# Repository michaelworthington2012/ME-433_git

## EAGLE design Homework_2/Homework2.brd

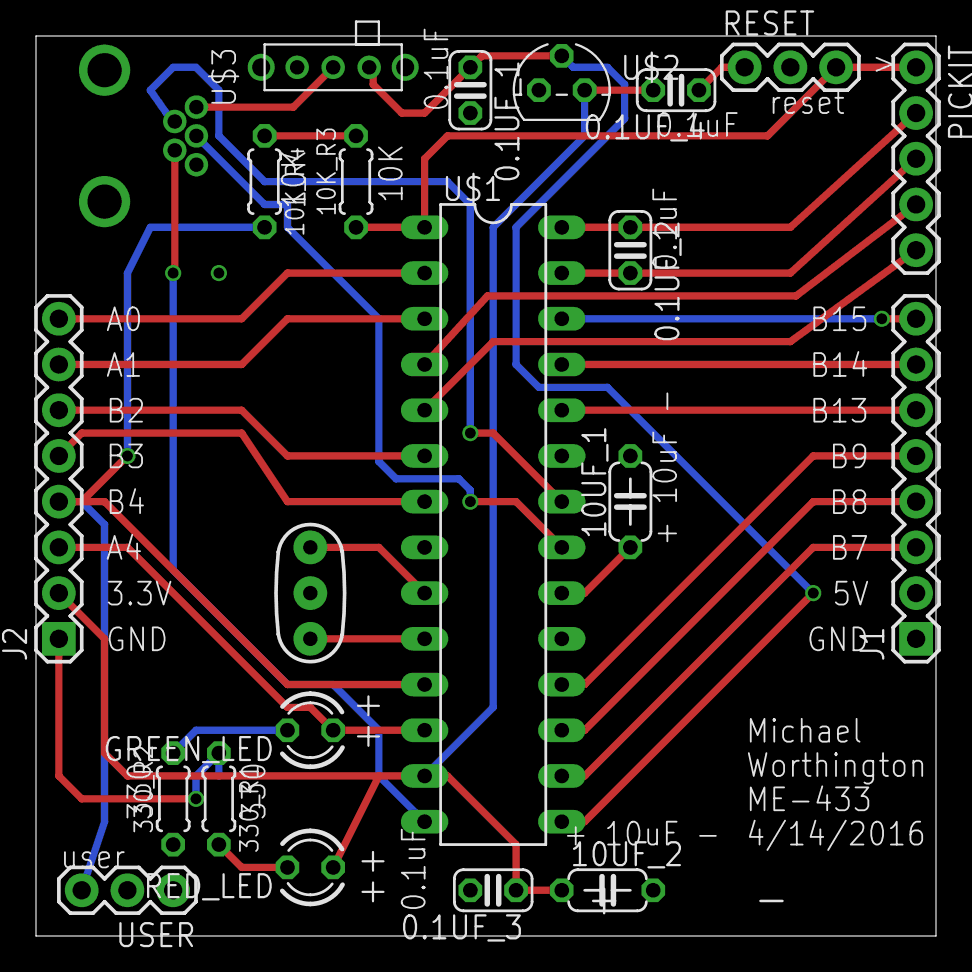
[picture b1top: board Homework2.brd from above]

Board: 2 copper layers, 50.0 x 50.0 mm, 22 parts (0 on the bottom side), 28 nets.

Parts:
0.1UF_1, 0.1UF_2, 0.1UF_3, 0.1UF_4: C025-024X044
8MHZRES: RESONATOR-PTH
10K_R3, 10K_R4, 330_R1, 330_R2: 0204/5
10UF_1, 10UF_2: C050-024X044
GREEN_LED: LED3MM
J1, J2: 1X08
PICKIT: 1X05
RED_LED: LED3MM
RESET: 1X03
U$1: PIC32; DIL28-3
U$2: MCP1702; TO92
U$3: USB_B_PCB; USB-MB-H
U$4: SLIDER_SWITCH; SLIDER_FOOTPRINT
USER: 1X03

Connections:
+3V3: 10K_R3.2, 10K_R4.1
A0: J2.8, U$1.2
A1: J2.7, U$1.3
A4: GREEN_LED.A, J2.3, U$1.12
B2: J2.6, U$1.6
B3: J2.5, U$1.7
B4: 10K_R4.2, J2.4, U$1.11, USER.3
B7: J1.3, U$1.16
B8: J1.4, U$1.17
B9: J1.5, U$1.18
B13: J1.6, U$1.24
B14: J1.7, U$1.25
B15: J1.8, U$1.26
D+: U$1.21, U$3.D+
D-: U$1.22, U$3.D-
GND: 0.1UF_1.2, 0.1UF_2.2, 0.1UF_3.2, 0.1UF_4.1, 8MHZRES.2, 10UF_1.2, 10UF_2.2, 330_R1.1, 330_R2.1, J1.1, J2.1, PICKIT.3, RESET.1, U$1.8, U$1.19, U$1.27, U$2.1, U$3.GND, USER.1
MCLR: 10K_R3.1, PICKIT.1, RESET.3, U$1.1
unnamed: 330_R2.2, GREEN_LED.K
unnamed: 330_R1.2, RED_LED.K
unnamed: 0.1UF_2.1, PICKIT.2, U$1.23, U$1.28
unnamed: 10UF_1.1, U$1.20
OSC1: 8MHZRES.1, U$1.9
OSC2: 8MHZRES.3, U$1.10
PGEC1: PICKIT.5, U$1.5
PGED1: PICKIT.4, U$1.4
USBID: U$1.14, U$3.ID
VBUS+5: 0.1UF_1.1, J1.2, U$1.15, U$2.2, U$3.VBUS, U$4.2.PIN2, U$4.3.PIN3
VDD: 0.1UF_3.1, 0.1UF_4.2, 10UF_2.1, J2.2, RED_LED.A, U$1.13, U$2.3

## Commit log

2016-04-04 HW1_commit 1
    Just created a blank main.c file
2016-04-04 HW1_commit 2
    After initializing in main and checking to see if LED works
2016-04-04 HW1_commit3
    Light toggling at .5ms
2016-04-05 HW1_commit4
    Working LED with _CP0_SET and GET
2016-04-05 HW1_part 2
    Noisy Channel of Scope before CAP
2016-04-05 HW1_Pt2
    clean channel after adding Cap between output and ground
2016-04-05 HW1_final part
    Scoped channel of .5mHz blinking
2016-04-05 HW1_pt1
    circuit diagram
2016-04-07 HW2_first commit
    Gathered first libraries and created one part
2016-04-13 homework2/3_commit3
    beginning schematic routing
2016-04-13 Homework2/3_commit4
    more schematic work
2016-04-14 Homework_2/3_commit#5
    finished schematic
2016-04-14 homework_2/3_commit#6
    brd before error checking
2016-04-14 Ready to be checked before order
2016-04-14 homework_2/3_commit#7(?)
    commit after submitting final gerber
2016-05-24 Homework 11 Cad
    pictures (cad and real)
2016-05-24 Homework10 Wheel pictures
    pictures of wheels
2016-05-24 Homework 11 wheel files
2016-05-24 Homework 9
    android Hello world
2016-05-24 Homework 9.1
    more files from studio
2016-05-24 Homework 9.2
    Working hello world picture
2016-05-24 Homework 9.3
    …gitignore
2016-05-24 Homework 6
    Working IMU pics
2016-05-28 lcd screen work
2016-05-28 running homework 1 on new board
2016-05-28 board files
2016-05-28 more android files
2016-05-28 finished soldered pcb
2016-05-31 Working LCD Screen code
2016-05-31 Picture of hello world
2016-05-31 updated string making function
2016-06-05 Android side of CDC working
2016-06-09 Final Project Files
2016-06-09 more updates for final commit

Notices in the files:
parts and their libraries:
SparkFun-FreqCtrl: Licensing: Creative Commons ShareAlike 4.0 International - https://creativecommons.org/licenses/by-sa/4.0
